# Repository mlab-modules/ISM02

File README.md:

# ISM02 - Long Range, Low Power, sub-GHz RF Transceiver

ISM02A is a telemetry module based on the Semtech SX1262 RF transceiver. This module is widely used in LoRa and other sub-GHz wireless communication applications. It incorporates an RF switch (PE4259) to multiplex RX and TX on a single antenna, making it a compact solution for IoT and telemetry use cases.

## Features
- **RF Transceiver:** [SX1262](https://www.semtech.com/products/wireless-rf/lora-transceivers/sx1262)
  - More power-efficient compared to the SX127x series
  - Additional features with a smaller footprint and fewer external components
  - Operating frequency range: 150 MHz to 960 MHz
  - Supports LoRa and (G)FSK modulation
  - Maximum output power: +22 dBm
  - Low power consumption: 4.2 mA in receive mode
  - Complies with ETSI EN 300 220, FCC CFR 47 Part 15, and other global ISM band regulations
- **RF Switch:** [PE4259](https://www.psemi.com/products/rf-switches/pe4259) UltraCMOS RF switch
  - Frequency range: 10 MHz – 3000 MHz
  - Low insertion loss: 0.35 dB @ 1000 MHz
  - High isolation: 30 dB @ 1000 MHz
  - High ESD tolerance of 2 kV HBM
  - Used to multiplex RX and TX on a single antenna

The module is typically used as a LoRa device and offers flexible wireless communication for various low-power, long-range applications.

## Applications
- Remote sensors
- Agricultural sensors
- HAB/stratospheric balloon tracking and telemetry
- Remote control applications (UAVs, Robots)

## Specifications

| Parameter          | Value                        | Description                      |
|--------------------|------------------------------|----------------------------------|
| Dimensions         | 50.292 x 29.972 mm            | Physical size of the module      |
| Frequency Range    | 150 MHz – 960 MHz             | Supports sub-GHz ISM bands       |
| Modulation Types   | LoRa, FSK                     | Supports LoRaWAN and proprietary |
| Max Output Power   | +22 dBm                       | Using SX1262                     |
| Power Consumption  | 4.2 mA in Rx mode             | Low power consumption            |
| RF Switch          | PE4259                        | Used for antenna multiplexing    |

## Additional Resources
- [SX1262 Datasheet](https://www.semtech.com/products/wireless-rf/lora-transceivers/sx1262)
- [PE4259 Datasheet](https://www.psemi.com/products/rf-switches/pe4259)

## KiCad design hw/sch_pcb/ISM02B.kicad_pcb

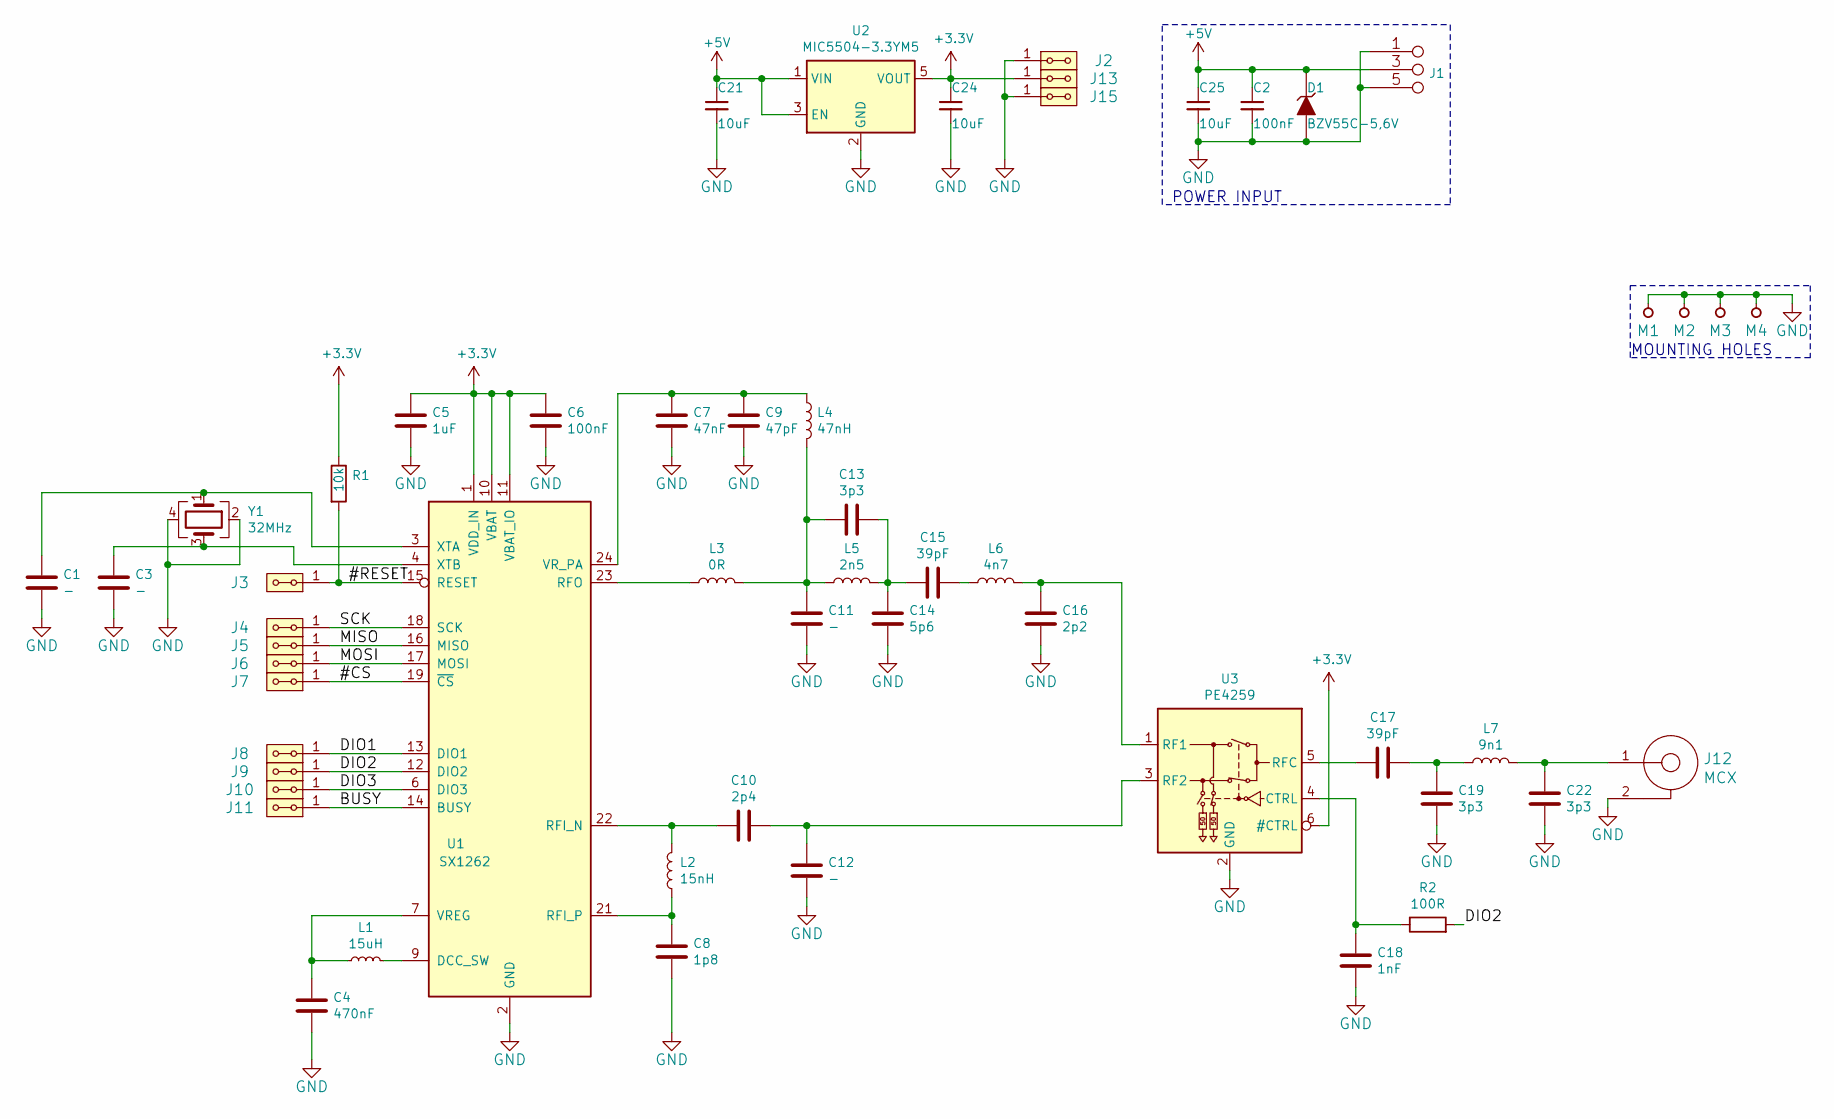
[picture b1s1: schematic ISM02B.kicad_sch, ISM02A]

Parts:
C1, C3, C11, C12: -; C_0603_1608Metric_Pad1.05x0.95mm_HandSolder
C2, C6: 100nF; C_0603_1608Metric_Pad1.05x0.95mm_HandSolder
C4: 470nF; C_0603_1608Metric_Pad1.05x0.95mm_HandSolder
C5: 1uF; C_0603_1608Metric_Pad1.05x0.95mm_HandSolder
C7: 47nF; C_0603_1608Metric_Pad1.05x0.95mm_HandSolder
C8: 1p8; C_0603_1608Metric_Pad1.05x0.95mm_HandSolder
C9: 47pF; C_0603_1608Metric_Pad1.05x0.95mm_HandSolder
C10: 2p4; C_0603_1608Metric_Pad1.05x0.95mm_HandSolder
C13, C19, C22: 3p3; C_0603_1608Metric_Pad1.05x0.95mm_HandSolder
C14: 5p6; C_0603_1608Metric_Pad1.05x0.95mm_HandSolder
C15, C17: 39pF; C_0603_1608Metric_Pad1.05x0.95mm_HandSolder
C16: 2p2; C_0603_1608Metric_Pad1.05x0.95mm_HandSolder
C18: 1nF; C_0603_1608Metric_Pad1.05x0.95mm_HandSolder
C21, C24, C25: 10uF; SMD-0805
D1: BZV55C-5,6V; Diode-MiniMELF_Standard
J1: JUMP_3X2; Straight_2x03
J2, J3, J4, J5, J6, J7, J8, J9, J10, J11, J13, J15: HEADER_2x01_PARALLEL; Straight_2x01
J12: MCX
L1: 15uH; SMD-0805
L2: 15nH; L_0402_1005Metric
L3: 0R; L_0402_1005Metric
L4: 47nH; L_0402_1005Metric
L5: 2n5; L_0402_1005Metric
L6: 4n7; L_0402_1005Metric
L7: 9n1; L_0402_1005Metric
M1, M2, M3, M4: HOLE; MountingHole_3mm
R1: 10k; SMD-0603
R2: 100R; SMD-0603
U1: SX1262; QFN-24-1EP_4x4mm_P0.5mm_EP2.6x2.6mm_ThermalVias
U2: MIC5504-3.3YM5; SOT-23-5
U3: PE4259; SOT-363_SC-70-6
Y1: 32MHz; Crystal_SMD_NX2016SA

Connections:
+3V3: C5.1, C6.1, C24.1, J13.1, J13.2, R1.1, U1.1 (VDD_IN), U1.10 (VBAT), U1.11 (VBAT_IO), U2.5 (VOUT), U3.6 (#CTRL)
+5V: C2.1, C21.1, C25.1, D1.1 (K), J1.3 (4), J1.4, U2.1 (VIN), U2.3 (EN)
/#CS: J7.1, J7.2, U1.19 (~CS~)
/#RESET: J3.1, J3.2, R1.2, U1.15 (RESET)
/BUSY: J11.1, J11.2, U1.14 (BUSY)
/DIO1: J8.1, J8.2, U1.13 (DIO1)
/DIO2: J9.1, J9.2, R2.2, U1.12 (DIO2)
/DIO3: J10.1, J10.2, U1.6 (DIO3)
/MISO: J5.1, J5.2, U1.16 (MISO)
/MOSI: J6.1, J6.2, U1.17 (MOSI)
/SCK: J4.1, J4.2, U1.18 (SCK)
GND: C1.2, C2.2, C3.2, C4.2, C5.2, C6.2, C7.2, C8.2, C9.2, C11.2, C12.2, C14.2, C16.2, C18.2, C19.1, C21.2, C22.1, C24.2, C25.2, D1.2 (A), J1.1 (2), J1.2, J1.5 (6), J1.6, J2.1, J2.2, J12.2, J15.1, J15.2, M1.1, M2.1, M3.1, M4.1, U1.2 (GND), U1.5 (GND), U1.8 (GND), U1.20 (GND), U1.25 (GND), U2.2 (GND), U3.2 (GND), Y1.2, Y1.4
unnamed: C1.1, U1.3 (XTA), Y1.1
unnamed: C3.1, U1.4 (XTB), Y1.3
unnamed: C4.1, L1.1, U1.7 (VREG)
unnamed: C7.1, C9.1, L4.1, U1.24 (VR_PA)
unnamed: C8.1, L2.1, U1.21 (RFI_P)
unnamed: C10.1, C12.1, U3.3 (RF2)
unnamed: C10.2, L2.2, U1.22 (RFI_N)
unnamed: C11.1, C13.2, L3.2, L4.2, L5.1
unnamed: C13.1, C14.1, C15.2, L5.2
unnamed: C15.1, L6.1
unnamed: C16.1, L6.2, U3.1 (RF1)
unnamed: C17.1, C19.2, L7.1
unnamed: C17.2, U3.5 (RFC)
unnamed: C18.1, R2.1, U3.4 (CTRL)
unnamed: C22.2, J12.1, L7.2
unnamed: L1.2, U1.9 (DCC_SW)
unnamed: L3.1, U1.23 (RFO)

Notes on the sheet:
MOUNTING HOLES
POWER INPUT

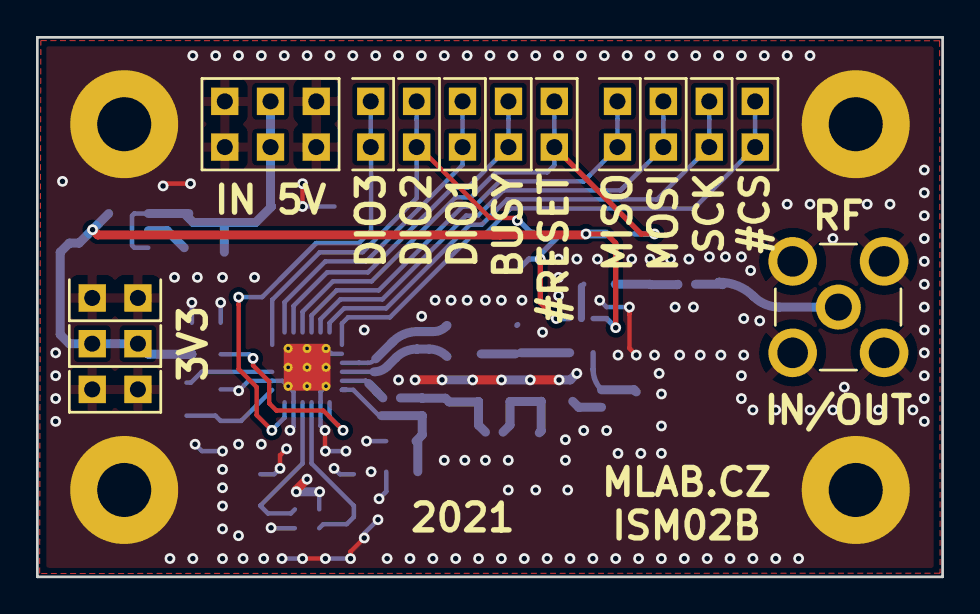
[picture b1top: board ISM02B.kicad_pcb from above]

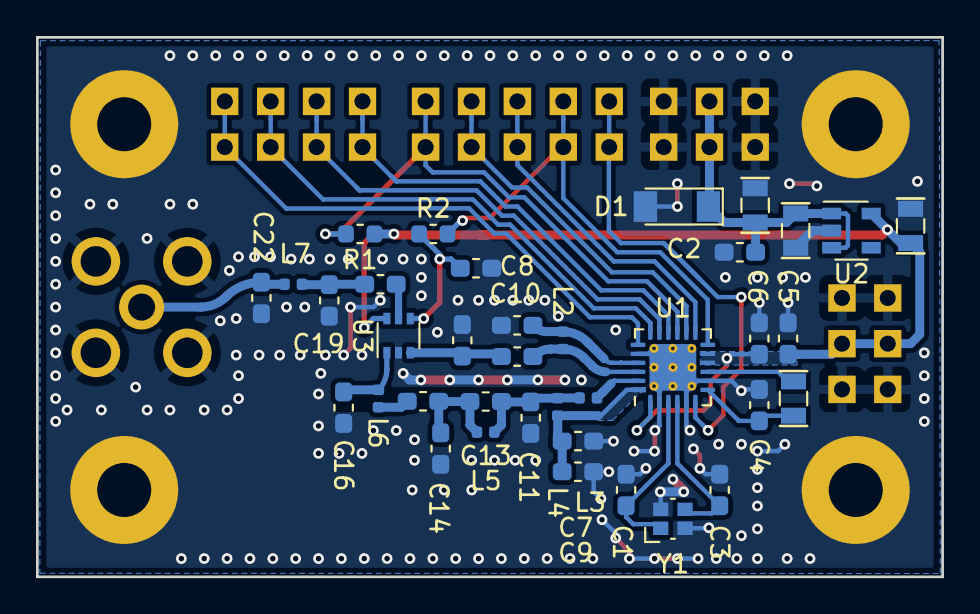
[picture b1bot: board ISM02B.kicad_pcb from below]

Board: 2 copper layers, 50.3 x 30.0 mm, 55 parts (37 on the bottom side), 29 nets.

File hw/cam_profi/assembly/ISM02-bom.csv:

Component,Description,Part,References,Value,Footprint,Quantity Per PCB,Datasheet,mfpn,ust_id
1,,C-Device-ISM02A-rescue,C8,1p8,C_0603_1608Metric_Pad1.05x0.95mm_HandSolder,1,,"C0G 0,1pF 50V",5dad52a4128750448eca18e8
2,,C-Device-ISM02A-rescue,C16,2p2,C_0603_1608Metric_Pad1.05x0.95mm_HandSolder,1,,"C0G 0,1pF 50V",5c70984812875079b91f8bdd
3,,C-Device-ISM02A-rescue,C10,2p4,C_0603_1608Metric_Pad1.05x0.95mm_HandSolder,1,,"C0G 0,1pF 50V",5dad53d8128750448eca1906
4,,C-Device-ISM02A-rescue,C13C19C22,3p3,C_0603_1608Metric_Pad1.05x0.95mm_HandSolder,3,,"C0G 0,1pF 50V",5cd09016128750448e45434f
5,,C-Device-ISM02A-rescue,C14,5p6,C_0603_1608Metric_Pad1.05x0.95mm_HandSolder,1,,"C0G 0,25pF 50V",5dad5450128750448eca1919
6,,C-Device-ISM02A-rescue,C15C17,39pF,C_0603_1608Metric_Pad1.05x0.95mm_HandSolder,2,,C0G 5% 50V,5dad549f128750448eca1926
7,,C-Device-ISM02A-rescue,C9,47pF,C_0603_1608Metric_Pad1.05x0.95mm_HandSolder,1,,C0G 5% 50V,5dad5314128750448eca18f7
8,Unpolarized capacitor,C,C18,1nF,C_0603_1608Metric_Pad1.05x0.95mm_HandSolder,1,~,,5c70984812875079b91f8bec
9,,C-Device-ISM02A-rescue,C7,47nF,C_0603_1608Metric_Pad1.05x0.95mm_HandSolder,1,,X7R 1% 16V,5dad51cf128750448eca18d8
10,,C_Small-Device-ISM02A-rescue,C2,100nF,C_0603_1608Metric_Pad1.05x0.95mm_HandSolder,1,,,C0805_100n
11,,C-Device-ISM02A-rescue,C6,100nF,C_0603_1608Metric_Pad1.05x0.95mm_HandSolder,1,,,5c70984812875079b91f8bf2
12,,C-Device-ISM02A-rescue,C4,470nF,C_0603_1608Metric_Pad1.05x0.95mm_HandSolder,1,,X5R 10% 10V,5dad50c1128750448eca18c6
13,,C-Device-ISM02A-rescue,C5,1uF,C_0603_1608Metric_Pad1.05x0.95mm_HandSolder,1,,,5c70984812875079b91f8bc2
14,,C_Small-Device-ISM02A-rescue,C21C24C25,10uF,SMD-0805,3,,,5c70984812875079b91f8bbe
15,,C-Device-ISM02A-rescue,C1C3C11C12,-,C_0603_1608Metric_Pad1.05x0.95mm_HandSolder,4,,,
16,,D_ZENER-MLAB_D,D1,"BZV55C-5,6V",Diode-MiniMELF_Standard,1,,,5c70984512875079b91f88b2
17,,HEADER_2x01_PARALLEL-MLAB_HEADER,J2J3J4J5J6J7J8J9J10J11J13J15,HEADER_2x01_PARALLEL,Straight_2x01,12,,,
18,,JUMP_3X2-MLAB_Jumpers,J1,JUMP_3X2,Straight_2x03,1,,,
19,,SMA-MLAB_CONNECTORS,J12,MCX,MCX,1,,,
20,,L-Device-ISM02A-rescue,L3,0R,L_0402_1005Metric,1,,,5c70984512875079b91f8949
21,,L-Device-ISM02A-rescue,L5,2n5,L_0402_1005Metric,1,,LQW15AN2N5C00D,5dad56ff128750448eca1975
22,,L-Device-ISM02A-rescue,L6,4n7,L_0402_1005Metric,1,,LQW15AN4N7C00D,5dad574f128750448eca1986
23,,L-Device-ISM02A-rescue,L7,9n1,L_0402_1005Metric,1,,LQW15AN9N1H00D,5dad5789128750448eca1995
24,,L-Device-ISM02A-rescue,L2,15nH,L_0402_1005Metric,1,,LQW15AN15NH00D,5dad566c128750448eca1959
25,,L-Device-ISM02A-rescue,L4,47nH,L_0402_1005Metric,1,,LQW15AN47NJ00D,5dad56ba128750448eca1968
26,,L_Small-Device-ISM02A-rescue,L1,15uH,SMD-0805,1,,MLZ2012M150W 0805,5dad55e8128750448eca1941
27,Resistor,R,R2,100R,SMD-0603,1,~,,5c70984512875079b91f8956
28,,R-Device-ISM02A-rescue,R1,10k,SMD-0603,1,,,5c70984512875079b91f8962
29,,MIC5504-3.3YM5-Regulator_Linear-ISM02A-rescue,U2,MIC5504-3.3YM5,SOT-23-5,1,http://ww1.microchip.com/downloads/en/DeviceDoc/MIC550X.pdf,,5c7255e81287500b4e112ea2
30,RF Switch,PE4259,U3,PE4259,SOT-363_SC-70-6,1,https://www.psemi.com/pdf/datasheets/pe4259ds.pdf,,5face19b12875025b3977e15
31,,SX1262-MLAB_IO-ISM02A-rescue,U1,SX1262,QFN-24-1EP_4x4mm_P0.5mm_EP2.6x2.6mm_ThermalVias,1,,,5dad5866128750448eca19a4
32,,Crystal_GND24-Device-ISM02A-rescue,Y1,32MHz,Crystal_SMD_NX2016SA,1,,NX2016SA-32M-EXS00A-CS06465,5dad592b128750448eca19b2

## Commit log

2019-10-10 [MLABweb] Documentation edits; ISM02A
2019-10-14 ISM02A edit schema
2019-10-16 ISM02 - edit schema
2019-10-18 ISM02A schema
2019-10-21 Přidání datasheetu.
2019-10-28 Prvni verze layoutu
2019-11-05 Pridana stinici krabicka, upravene rozmery, pridane prokovy
2019-11-08 Generovana vyrobni data
2019-11-14 Uprava dat pro osazovani
2020-05-04 The basic photos of new modules.
2020-10-28 Documentation improvement.
2020-10-28 Update schematics export and crop images.
2020-10-28 Fix license.
2021-03-23 Edit
2021-03-23 Edit 02B
2021-03-25 Remove unused 1 mark from power connector.
2021-03-26 Edit images
2021-04-16 Revert "Edit"
    This reverts commit 3bfea5ab87054fd9b05002ed626080fed2685c40.
2022-02-17 Improving documentation from MLAB web.
2022-04-06 automated commit; add github actions
2022-04-06 Update actions products
2023-02-02 Cleanup activate github actions.
2023-02-03 Update title block.
2023-02-13 update actions
2023-02-13 Update metadata files
2023-02-13 resave in newer kicad
2023-02-14 Update workflow files
2023-07-20 update gitmodules
2023-07-20 kicad 7
2023-07-20 follow new naming style
2023-07-20 update assets
2023-07-20 assets
2023-09-16 Update status
2024-09-29 Updating documentation and readme.
2024-09-29 Remove unused file.
2025-01-22 Update datasheet.

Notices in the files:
hw/sch_pcb/ISM02B.kicad_sch:
GPL 3.0
